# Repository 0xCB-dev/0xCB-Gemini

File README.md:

# 0xCB-Gemini

### 0xCB Helios little brother - waveshare zero compatible

|                              Licence                               |                                                      OSHWA                                                       |
| :----------------------------------------------------------------: | :--------------------------------------------------------------------------------------------------------------: |
|  |  |

### Official vendors

Purchasing Gemini from any vendors listed here directly supports our work. Gemini controllers sourced from vendors not listed here and not produced by us will not receive the same level of support and may have varying degrees of quality.

### EU:

Germany: [KeebSupply](https://keeb.supply/products/0xcb-gemini)

Germany: [Keycapsss](https://keycapsss.com/keyboard-parts/mcu-controller/277/0xcb-gemini-waveshare-rp2040-zero-compatible-microcontroller)

### North America:

America: Ringer Keys (Coming soon!)

#### Flashing

- `qmk clone`
- `cd qmk_firmware`
- To go to bootloader press the reset button longer than 500ms and release. Alternatively you can short the RST pin to GND, as it's wired to the reset button.
- `make 0xcb/gemini:default:flash`

### Assembly

The PCBs are assembled at the fab with the production files located in the /kikit/prod/ dir.

### Integration in your own design

- Waveshare zero footprint
- more to come

### PCB

KiCad 8 stable

[Schematic](https://github.com/0xCB-dev/0xcb-Gemini/blob/main/rev1.0/gemini.pdf)

### Pinout

| GPIO | F1       | F2        | F3       | F4     | F5  | F6   | F7   | F8           | F9            |
| ---- | -------- | --------- | -------- | ------ | --- | ---- | ---- | ------------ | ------------- |
| 0    | SPI0 RX  | UART0 TX  | I2C0 SDA | PWM0 A | SIO | PIO0 | PIO1 |              | USB OVCUR DET |
| 1    | SPI0 CSn | UART0 RX  | I2C0 SCL | PWM0 B | SIO | PIO0 | PIO1 |              | USB VBUS DET  |
| 2    | SPI0 SCK | UART0 CTS | I2C1 SDA | PWM1 A | SIO | PIO0 | PIO1 |              | USB VBUS EN   |
| 3    | SPI0 TX  | UART0 RTS | I2C1 SCL | PWM1 B | SIO | PIO0 | PIO1 |              | USB OVCUR DET |
| 4    | SPI0 RX  | UART1 TX  | I2C0 SDA | PWM2 A | SIO | PIO0 | PIO1 |              | USB VBUS DET  |
| 5    | SPI0 CSn | UART1 RX  | I2C0 SCL | PWM2 B | SIO | PIO0 | PIO1 |              | USB VBUS EN   |
| 6    | SPI0 SCK | UART1 CTS | I2C1 SDA | PWM3 A | SIO | PIO0 | PIO1 |              | USB OVCUR DET |
| 7    | SPI0 TX  | UART1 RTS | I2C1 SCL | PWM3 B | SIO | PIO0 | PIO1 |              | USB VBUS DET  |
| 8    | SPI1 RX  | UART1 TX  | I2C0 SDA | PWM4 A | SIO | PIO0 | PIO1 |              | USB VBUS EN   |
| 9    | SPI1 CSn | UART1 RX  | I2C0 SCL | PWM4 B | SIO | PIO0 | PIO1 |              | USB OVCUR DET |
| 10   | SPI1 SCK | UART1 CTS | I2C1 SDA | PWM5 A | SIO | PIO0 | PIO1 |              | USB VBUS DET  |
| 11   | SPI1 TX  | UART1 RTS | I2C1 SCL | PWM5 B | SIO | PIO0 | PIO1 |              | USB VBUS EN   |
| 12   | SPI1 RX  | UART0 TX  | I2C0 SDA | PWM6 A | SIO | PIO0 | PIO1 |              | USB OVCUR DET |
| 13   | SPI1 CSn | UART0 RX  | I2C0 SCL | PWM6 B | SIO | PIO0 | PIO1 |              | USB VBUS DET  |
| 14   | SPI1 SCK | UART0 CTS | I2C1 SDA | PWM7 A | SIO | PIO0 | PIO1 |              | USB VBUS EN   |
| 15   | SPI1 TX  | UART0 RTS | I2C1 SCL | PWM7 B | SIO | PIO0 | PIO1 |              | USB OVCUR DET |
| 16   | SPI0 RX  | UART0 TX  | I2C0 SDA | PWM0 A | SIO | PIO0 | PIO1 |              | USB VBUS DET  |
| 17   | SPI0 CSn | UART0 RX  | I2C0 SCL | PWM0 B | SIO | PIO0 | PIO1 |              | USB VBUS EN   |
| 18   | SPI0 SCK | UART0 CTS | I2C1 SDA | PWM1 A | SIO | PIO0 | PIO1 |              | USB OVCUR DET |
| 19   | SPI0 TX  | UART0 RTS | I2C1 SCL | PWM1 B | SIO | PIO0 | PIO1 |              | USB VBUS DET  |
| 20   | SPI0 RX  | UART1 TX  | I2C0 SDA | PWM2 A | SIO | PIO0 | PIO1 | CLOCK GPIN0  | USB VBUS EN   |
| 21   | SPI0 CSn | UART1 RX  | I2C0 SCL | PWM2 B | SIO | PIO0 | PIO1 | CLOCK GPOUT0 | USB OVCUR DET |
| 22   | SPI0 SCK | UART1 CTS | I2C1 SDA | PWM3 A | SIO | PIO0 | PIO1 | CLOCK GPIN1  | USB VBUS DET  |
| 23   | SPI0 TX  | UART1 RTS | I2C1 SCL | PWM3 B | SIO | PIO0 | PIO1 | CLOCK GPOUT1 | USB VBUS EN   |
| 24   | SPI1 RX  | UART1 TX  | I2C0 SDA | PWM4 A | SIO | PIO0 | PIO1 | CLOCK GPOUT2 | USB OVCUR DET |
| 25   | SPI1 CSn | UART1 RX  | I2C0 SCL | PWM4 B | SIO | PIO0 | PIO1 | CLOCK GPOUT3 | USB VBUS DET  |
| 26   | SPI1 SCK | UART1 CTS | I2C1 SDA | PWM5 A | SIO | PIO0 | PIO1 |              | USB VBUS EN   |
| 27   | SPI1 TX  | UART1 RTS | I2C1 SCL | PWM5 B | SIO | PIO0 | PIO1 |              | USB OVCUR DET |
| 28   | SPI1 RX  | UART0 TX  | I2C0 SDA | PWM6 A | SIO | PIO0 | PIO1 |              | USB VBUS DET  |
| 29   | SPI1 CSn | UART0 RX  | I2C0 SCL | PWM6 B | SIO | PIO0 | PIO1 |              | USB VBUS EN   |

### Credits

Uses the same reset circuit found on the [0xCB-Helios](https://github.com/0xCB-dev/0xcb-Helios) which in turn is based on the one used on the [Sea-picro](https://github.com/joshajohnson/sea-picro) by joshajohnson and this very well written [article](https://acheronproject.com/reset_article_1/reset_article_1/) by the Acheron Project.

Thank you! :heart:

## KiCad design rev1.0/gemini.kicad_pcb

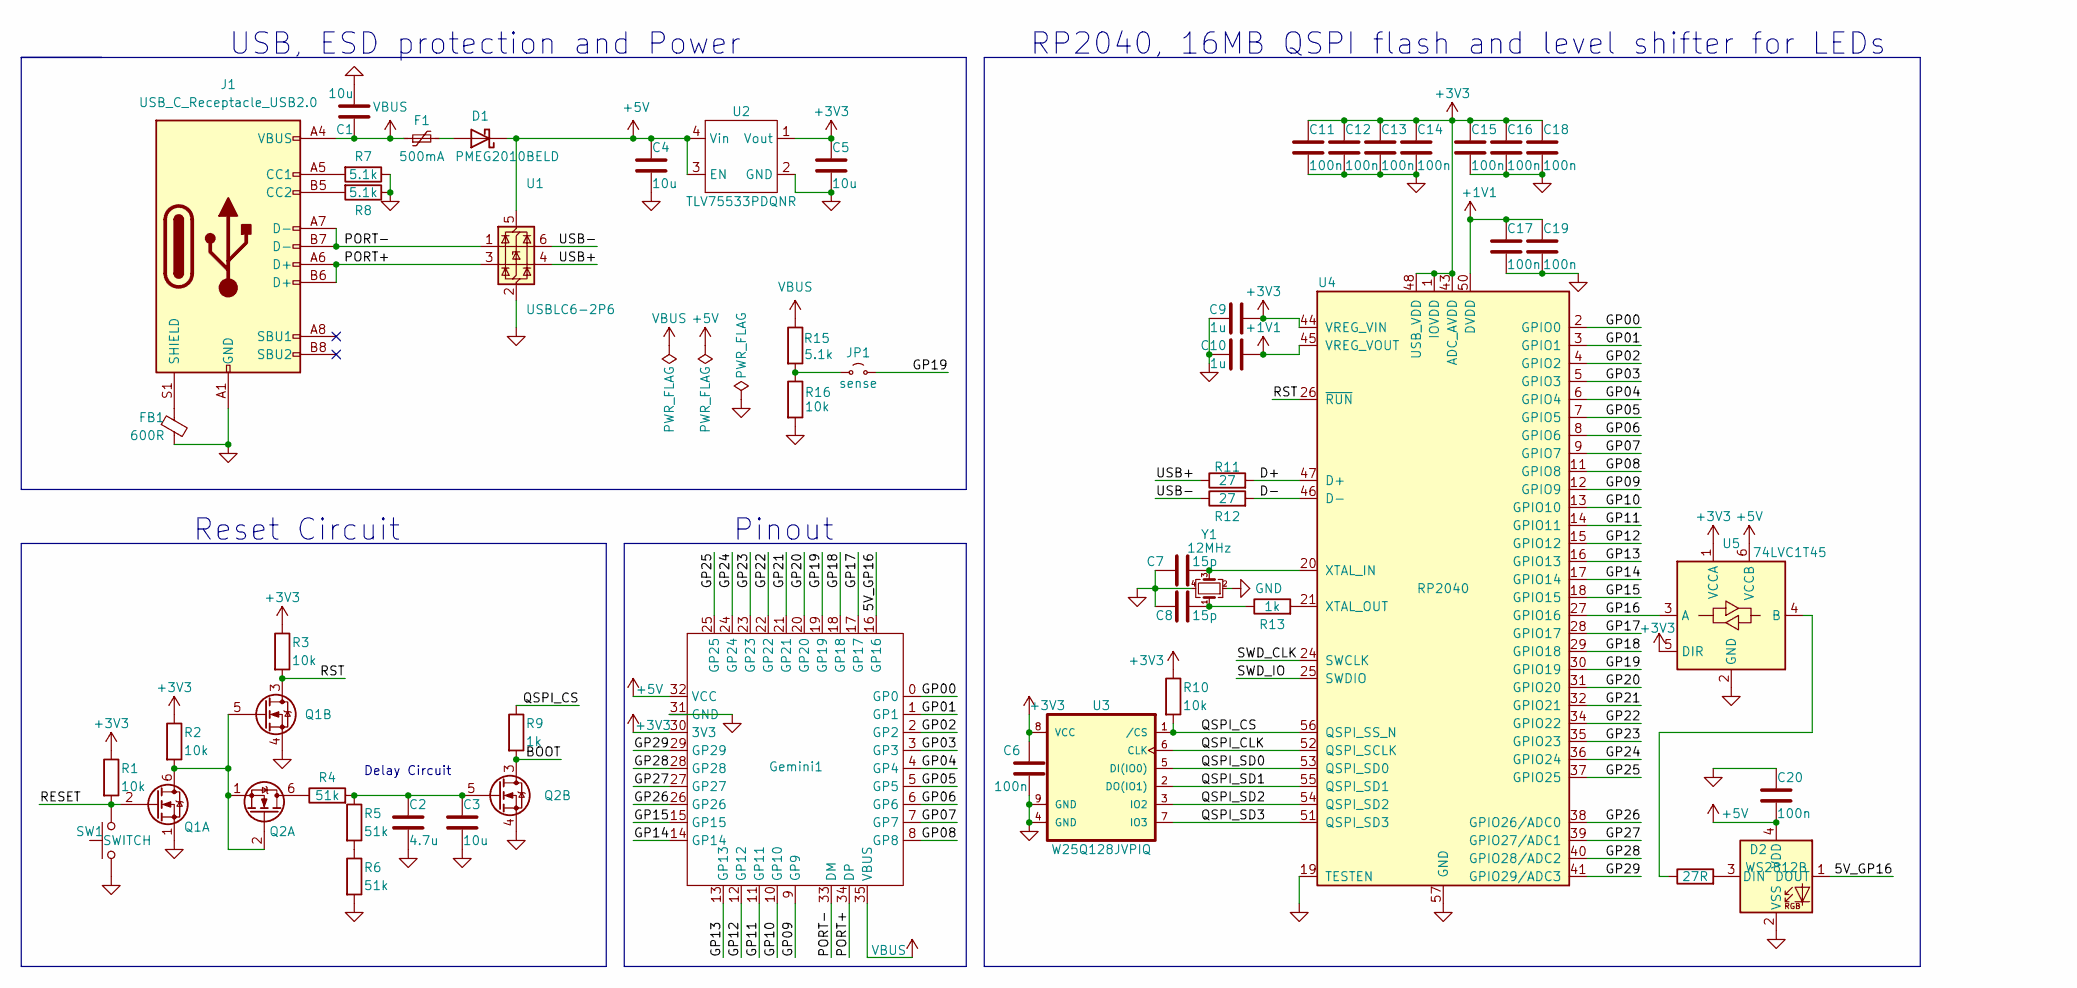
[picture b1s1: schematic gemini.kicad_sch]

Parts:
C1, C3, C4, C5: 10u; C_0402_1005Metric; MPN 10uF 20% 10V 0402; LCSC C15525
C2: 4.7u; C_0201_0603Metric; MPN 4.7uF 20% 10V 0402; LCSC C335103
C6, C11, C12, C13, C14, C15, C16, C17, C18, C19: 100n; C_0201_0603Metric; MPN 100nF 10% 10V 0402; LCSC C576431
C7, C8: 15p; C_0201_0603Metric; MPN 15pF 5% 10V; LCSC C85891
C9, C10: 1u; C_0201_0603Metric; MPN 1uF 20% 10V 0402; LCSC C76935
C20: 100n; C_0201_0603Metric; MPN CL05B104KO5NNNC; LCSC C576431
D1: PMEG2010BELD; SOD882D; MPN PMEG2010BELD,315; JLCPCB_CORRECTION 0; 0; 180
D2: WS2812B; LED_WS2812B-2020_PLCC4_2.0x2.0mm; MPN WS2812B-2020; LCSC C2976072
F1: 500mA; Fuse_0603_1608Metric; MPN MF-FSMF050X-2; LCSC C210357
FB1: 600R; R_0402_1005Metric; MPN BLM15PX601SN1D; LCSC C160977
Gemini1: gemini
J1: USB_C_Receptacle_USB2.0; USB_C_Receptacle_GCT_USB4105-xx-A_16P_TopMnt_Horizontal; MPN USB4510-03-1-A; JLCPCB_CORRECTION 0; -1; 0
JP1: sense; SolderJumper-Small
Q1, Q2: 2N7002VC-; SOT-563; MPN 2N7002VC; JLCPCB_CORRECTION 0; 0; 180
R1, R2, R3, R10, R16: 10k; R_0201_0603Metric; MPN 10k 1% 0402; LCSC C138117
R4, R5, R6: 51k; R_0201_0603Metric; MPN 51k 1% 0402; LCSC C295806
R7, R8, R15: 5.1k; R_0201_0603Metric; MPN 5.1k 1% 0402; LCSC C473460
R9, R13: 1k; R_0201_0603Metric; MPN 1k 1% 0402; LCSC C138297
R11, R12: 27; R_0201_0603Metric; MPN 27 1% 0402; LCSC C273295
R14: 27R; R_0201_0603Metric; MPN 0402WGF270JTCE; LCSC C273295
SW1: SWITCH; 1.9x2.8mm SW; MPN EVP-BL2A1B000; LCSC C589221
U1: USBLC6-2P6; SOT-666; MPN USBLC6-2P6; JLCPCB_CORRECTION 0; 0; 270
U2: TLV75533PDQNR; X2SON-4; MPN TLV75533PDQNR; JLCPCB_CORRECTION 0; 0; 180
U3: W25Q128JVPIQ; MPN W25Q128JVPIQ; JLCPCB_CORRECTION 0; 0; 270
U4: RP2040; RP2040-QFN-56; MPN SC0914(13); JLCPCB_CORRECTION 0; 0; 180
U5: 74LVC1T45; SOT-563; MPN SN74LVC1T45DRLR; JLCPCB_CORRECTION 0; 0; 270
Y1: 12MHz; Crystal_SMD_2520-4Pin_2.5x2.0mm; MPN ECS-120-10-36B-CWY-TR3; LCSC C2149204

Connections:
+1V1: C10.2, C17.1, C19.1, U4.23 (DVDD), U4.45 (VREG_VOUT), U4.50 (DVDD)
+3V3: C5.1, C6.1, C9.2, C11.1, C12.1, C13.1, C14.1, C15.1, C16.1, C18.1, Gemini1.30 (3V3), R1.1, R2.1, R3.1, R10.1, U2.1 (Vout), U3.8 (VCC), U4.1 (IOVDD), U4.10 (IOVDD), U4.22 (IOVDD), U4.33 (IOVDD), U4.42 (IOVDD), U4.43 (ADC_AVDD), U4.44 (VREG_VIN), U4.48 (USB_VDD), U4.49 (IOVDD), U5.1 (VCCA), U5.5 (DIR)
+5V: C4.1, C20.2, D1.1 (K), D2.4 (VDD), Gemini1.32 (VCC), U1.5 (VBUS), U2.3 (EN), U2.4 (Vin), U5.6 (VCCB)
/5V_GP16: D2.1 (DOUT), Gemini1.16 (GP16)
/BOOT: Q2.3 (D), R9.2
/D+: R11.2, U4.47 (D+)
/D-: R12.2, U4.46 (D-)
/GP00: Gemini1.0 (GP0), U4.2 (GPIO0)
/GP01: Gemini1.1 (GP1), U4.3 (GPIO1)
/GP02: Gemini1.2 (GP2), U4.4 (GPIO2)
/GP03: Gemini1.3 (GP3), U4.5 (GPIO3)
/GP04: Gemini1.4 (GP4), U4.6 (GPIO4)
/GP05: Gemini1.5 (GP5), U4.7 (GPIO5)
/GP06: Gemini1.6 (GP6), U4.8 (GPIO6)
/GP07: Gemini1.7 (GP7), U4.9 (GPIO7)
/GP08: Gemini1.8 (GP8), U4.11 (GPIO8)
/GP09: Gemini1.9 (GP9), U4.12 (GPIO9)
/GP10: Gemini1.10 (GP10), U4.13 (GPIO10)
/GP11: Gemini1.11 (GP11), U4.14 (GPIO11)
/GP12: Gemini1.12 (GP12), U4.15 (GPIO12)
/GP13: Gemini1.13 (GP13), U4.16 (GPIO13)
/GP14: Gemini1.14 (GP14), U4.17 (GPIO14)
/GP15: Gemini1.15 (GP15), U4.18 (GPIO15)
/GP16: U4.27 (GPIO16), U5.3 (A)
/GP17: Gemini1.17 (GP17), U4.28 (GPIO17)
/GP18: Gemini1.18 (GP18), U4.29 (GPIO18)
/GP19: Gemini1.19 (GP19), JP1.2 (B), U4.30 (GPIO19)
/GP20: Gemini1.20 (GP20), U4.31 (GPIO20)
/GP21: Gemini1.21 (GP21), U4.32 (GPIO21)
/GP22: Gemini1.22 (GP22), U4.34 (GPIO22)
/GP23: Gemini1.23 (GP23), U4.35 (GPIO23)
/GP24: Gemini1.24 (GP24), U4.36 (GPIO24)
/GP25: Gemini1.25 (GP25), U4.37 (GPIO25)
/GP26: Gemini1.26 (GP26), U4.38 (GPIO26/ADC0)
/GP27: Gemini1.27 (GP27), U4.39 (GPIO27/ADC1)
/GP28: Gemini1.28 (GP28), U4.40 (GPIO28/ADC2)
/GP29: Gemini1.29 (GP29), U4.41 (GPIO29/ADC3)
/PORT+: Gemini1.34 (DP), J1.A6 (D+), J1.B6 (D+), U1.3 (I/O2)
/PORT-: Gemini1.33 (DM), J1.A7 (D-), J1.B7 (D-), U1.1 (I/O1)
/QSPI_CLK: U3.6 (CLK), U4.52 (QSPI_SCLK)
/QSPI_CS: R9.1, R10.2, U3.1 (/CS), U4.56 (QSPI_SS_N)
/QSPI_SD0: U3.5 (DI(IO0)), U4.53 (QSPI_SD0)
/QSPI_SD1: U3.2 (DO(IO1)), U4.55 (QSPI_SD1)
/QSPI_SD2: U3.3 (IO2), U4.54 (QSPI_SD2)
/QSPI_SD3: U3.7 (IO3), U4.51 (QSPI_SD3)
/RESET: Q1.2 (G), R1.2, SW1.2
/RST: Q1.3 (D), R3.2, U4.26 (~RUN)
/SWD_CLK: U4.24 (SWCLK)
/SWD_IO: U4.25 (SWDIO)
/USB+: R11.1, U1.4 (I/O2)
/USB-: R12.1, U1.6 (I/O1)
GND: C1.2, C2.2, C3.2, C4.2, C5.2, C6.2, C7.1, C8.1, C9.1, C10.1, C11.2, C12.2, C13.2, C14.2, C15.2, C16.2, C17.2, C18.2, C19.2, C20.1, D2.2 (VSS), FB1.2, Gemini1.31 (GND), J1.A1 (GND), J1.A12 (GND), J1.B1 (GND), J1.B12 (GND), Q1.1 (S), Q1.4 (S), Q2.4 (S), R6.2, R7.1, R8.1, R16.2, SW1.1, U1.2 (GND), U2.2 (GND), U2.5 (TP), U3.4 (GND), U3.9 (GND), U4.19 (TESTEN), U4.57 (GND), U5.2 (GND), Y1.2, Y1.4
unnamed: C8.2, R13.1, Y1.1
unnamed: D1.2 (A), F1.2
unnamed: D2.3 (DIN), R14.2
unnamed: J1.A5 (CC1), R7.2
unnamed: J1.B5 (CC2), R8.2
unnamed: FB1.1, J1.S1 (SHIELD)
unnamed: JP1.1 (A), R15.2, R16.1
unnamed: Q1.5 (G), Q1.6 (D), Q2.1 (S), Q2.2 (G), R2.2
unnamed: Q2.6 (D), R4.1
unnamed: C2.1, C3.1, Q2.5 (G), R4.2, R5.1
unnamed: R5.2, R6.1
unnamed: C7.2, U4.20 (XTAL_IN), Y1.3
unnamed: R13.2, U4.21 (XTAL_OUT)
unnamed: R14.1, U5.4 (B)
VBUS: C1.1, F1.1, Gemini1.35 (VBUS), J1.A4 (VBUS), J1.A9 (VBUS), J1.B4 (VBUS), J1.B9 (VBUS), R15.1

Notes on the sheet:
RP2040, 16MB QSPI flash and level shifter for LEDs
USB, ESD protection and Power
Reset Circuit
Pinout
Delay Circuit

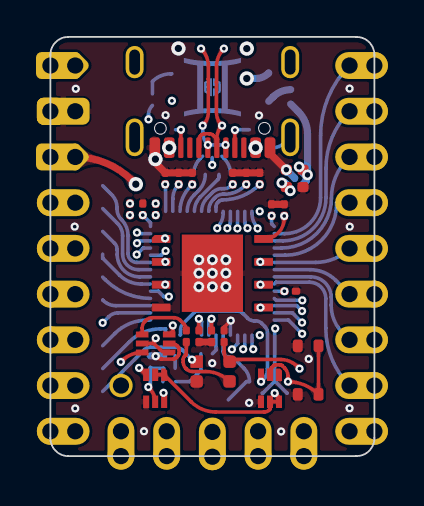
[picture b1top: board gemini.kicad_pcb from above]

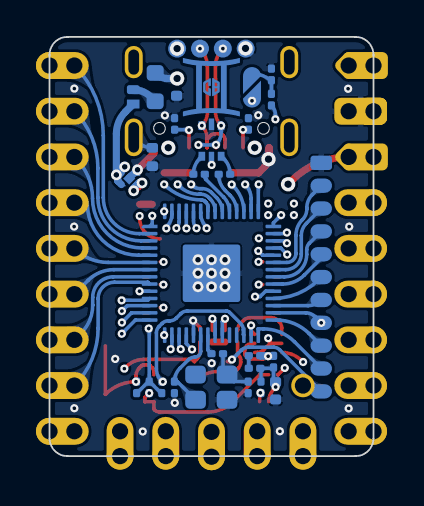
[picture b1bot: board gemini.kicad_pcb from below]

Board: 4 copper layers, 18.0 x 23.3 mm, 52 parts (26 on the bottom side), 65 nets.

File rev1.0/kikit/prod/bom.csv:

Comment,Designator,Footprint,LCSC
100n,"C6,C11,C12,C13,C14,C15,C16,C17,C18,C19,C20",gemini:C_0201_0603Metric,C576431
RP2040,U4,gemini:RP2040-QFN-56,C2040
10k,"R1,R2,R3,R10,R16",gemini:R_0201_0603Metric,C138117
15p,"C7,C8",gemini:C_0201_0603Metric,C85891
10u,"C1,C3,C4,C5",gemini:C_0402_1005Metric,C15525
51k,"R4,R5,R6",gemini:R_0201_0603Metric,C295806
1u,"C9,C10",gemini:C_0201_0603Metric,C76935
4.7u,C2,gemini:C_0201_0603Metric,C335103
2N7002VC-,"Q1,Q2",gemini:SOT-563,C504145
27,"R11,R12",gemini:R_0201_0603Metric,C273295
500mA,F1,gemini:Fuse_0603_1608Metric,C210357
SWITCH,SW1,gemini:1.9x2.8mm SW,C589221
USB_C_Receptacle_USB2.0,J1,gemini:USB_C_Receptacle_GCT_USB4105-xx-A_16P_TopMnt_Horizontal,C2858270
1k,"R9,R13",gemini:R_0201_0603Metric,C138297
PMEG2010BELD,D1,gemini:SOD882D,C552820
W25Q128JVPIQ,U3,gemini:W25Q128JVPIQ,C190862
5.1k,"R7,R8,R15",gemini:R_0201_0603Metric,C473460
27R,R14,gemini:R_0201_0603Metric,C273295
600R,FB1,gemini:R_0402_1005Metric,C160977
74LVC1T45,U5,gemini:SOT-563,C352970
TLV75533PDQNR,U2,gemini:X2SON-4,C2861882
12MHz,Y1,gemini:Crystal_SMD_2520-4Pin_2.5x2.0mm,C2149204
WS2812B,D2,gemini:LED_WS2812B-2020_PLCC4_2.0x2.0mm,C2976072
USBLC6-2P6,U1,gemini:SOT-666,C2827693

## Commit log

2024-09-05 add gemini
2024-09-13 Add oshwa
2024-09-13 Add oshwa id
